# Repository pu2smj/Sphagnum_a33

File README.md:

# Sphagnum_a33
IHM with cpu Allwinner A33

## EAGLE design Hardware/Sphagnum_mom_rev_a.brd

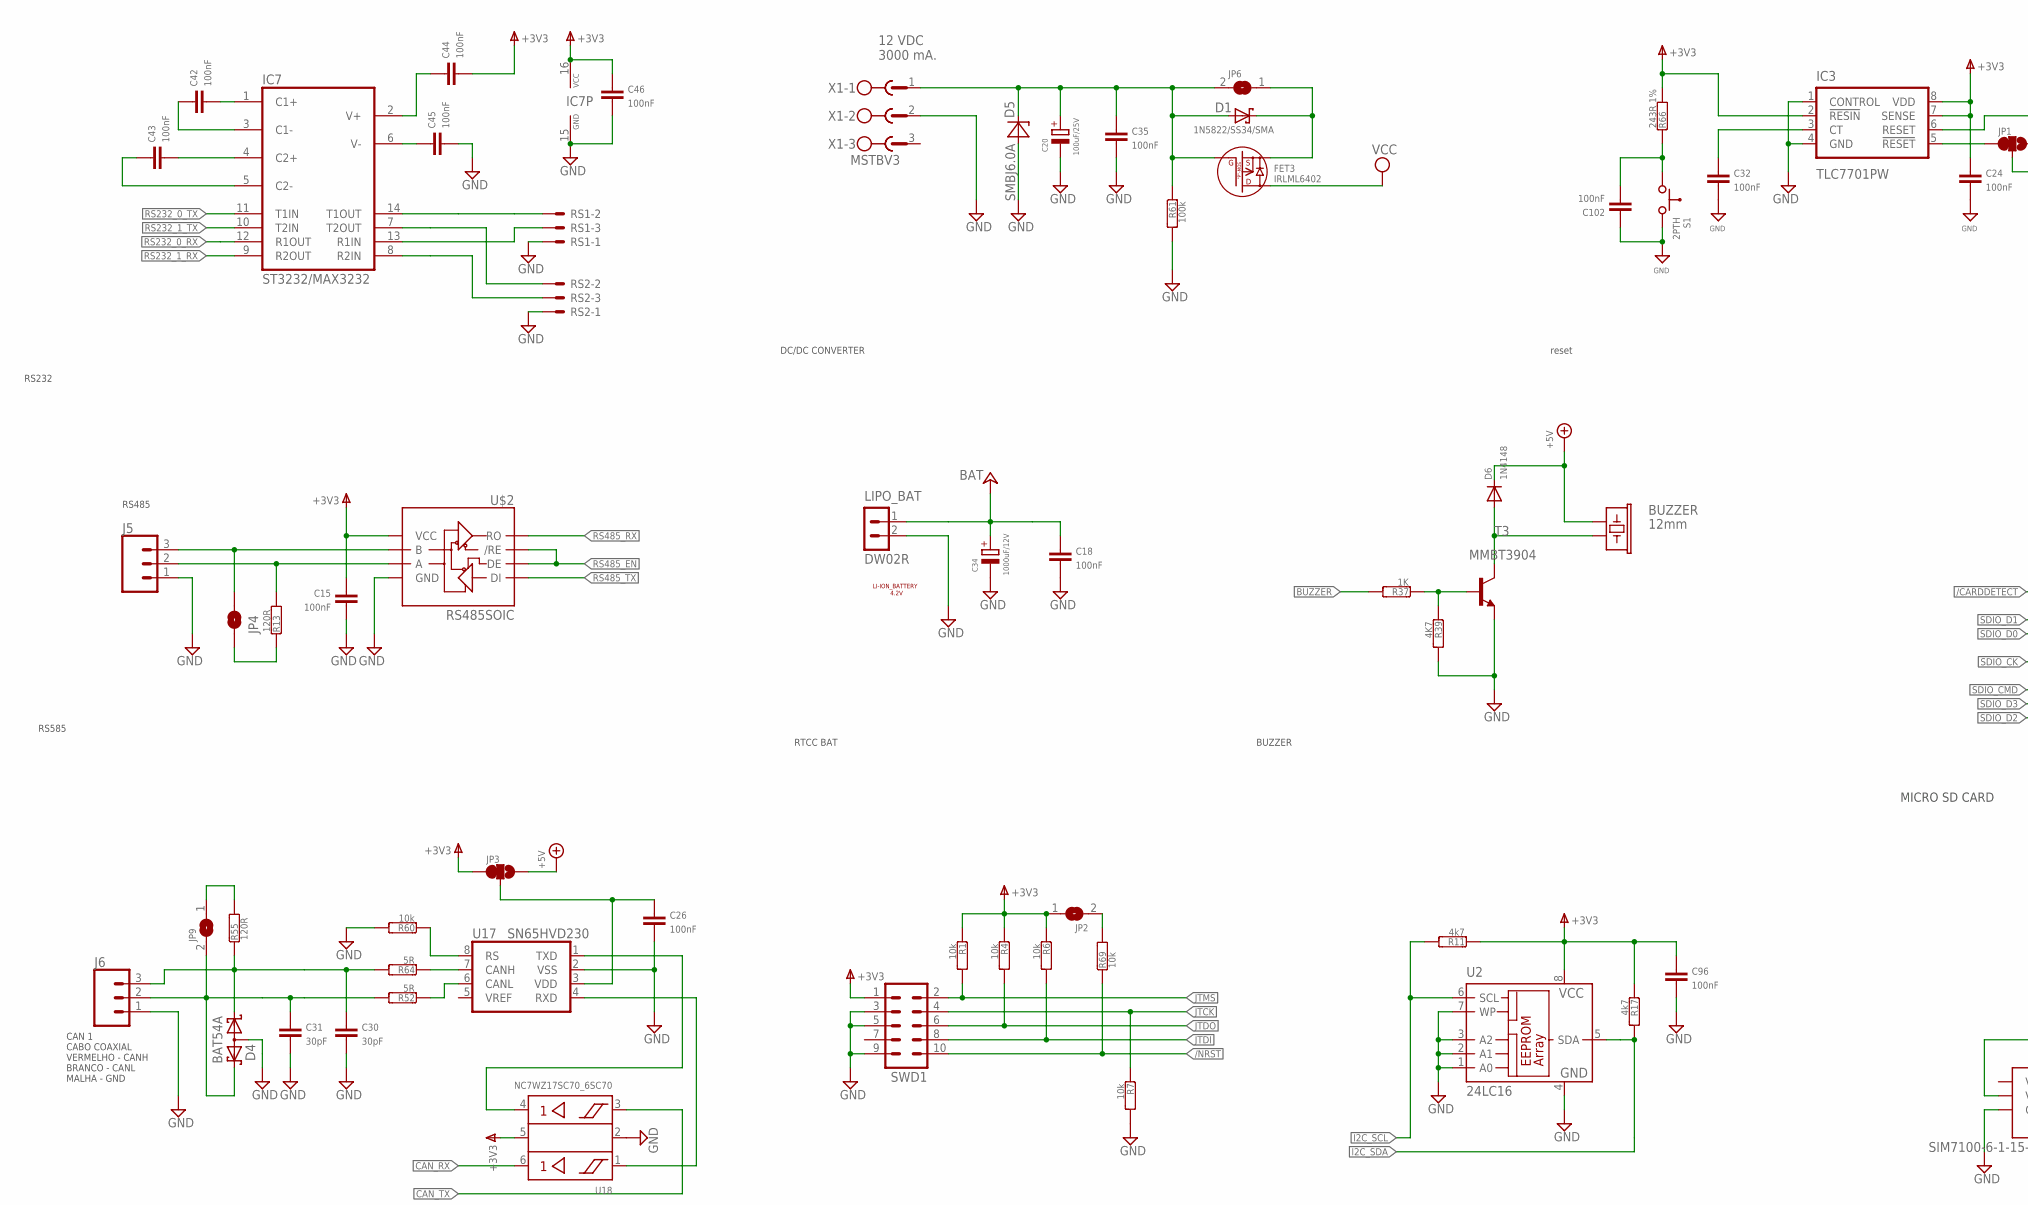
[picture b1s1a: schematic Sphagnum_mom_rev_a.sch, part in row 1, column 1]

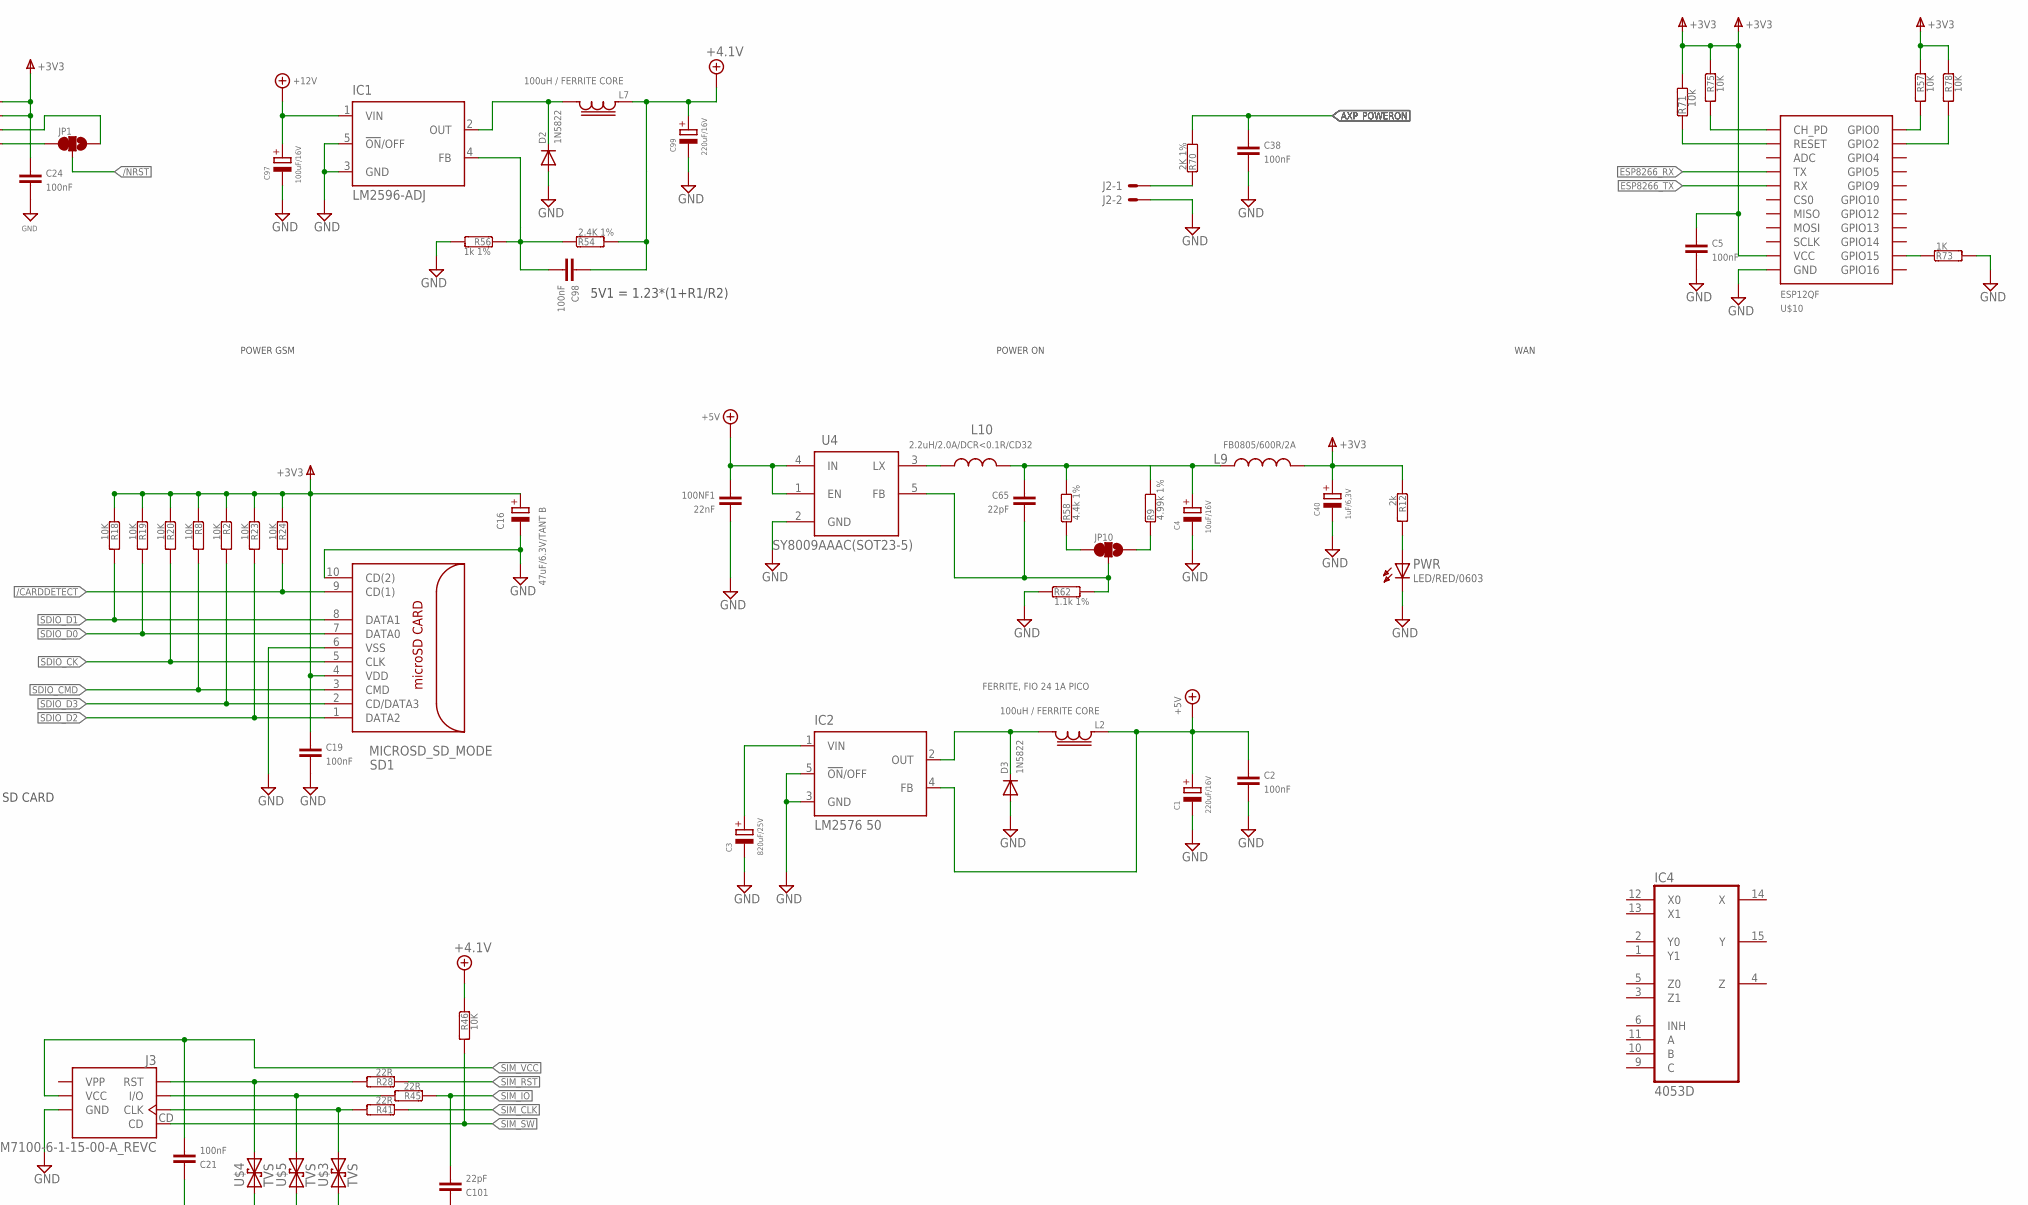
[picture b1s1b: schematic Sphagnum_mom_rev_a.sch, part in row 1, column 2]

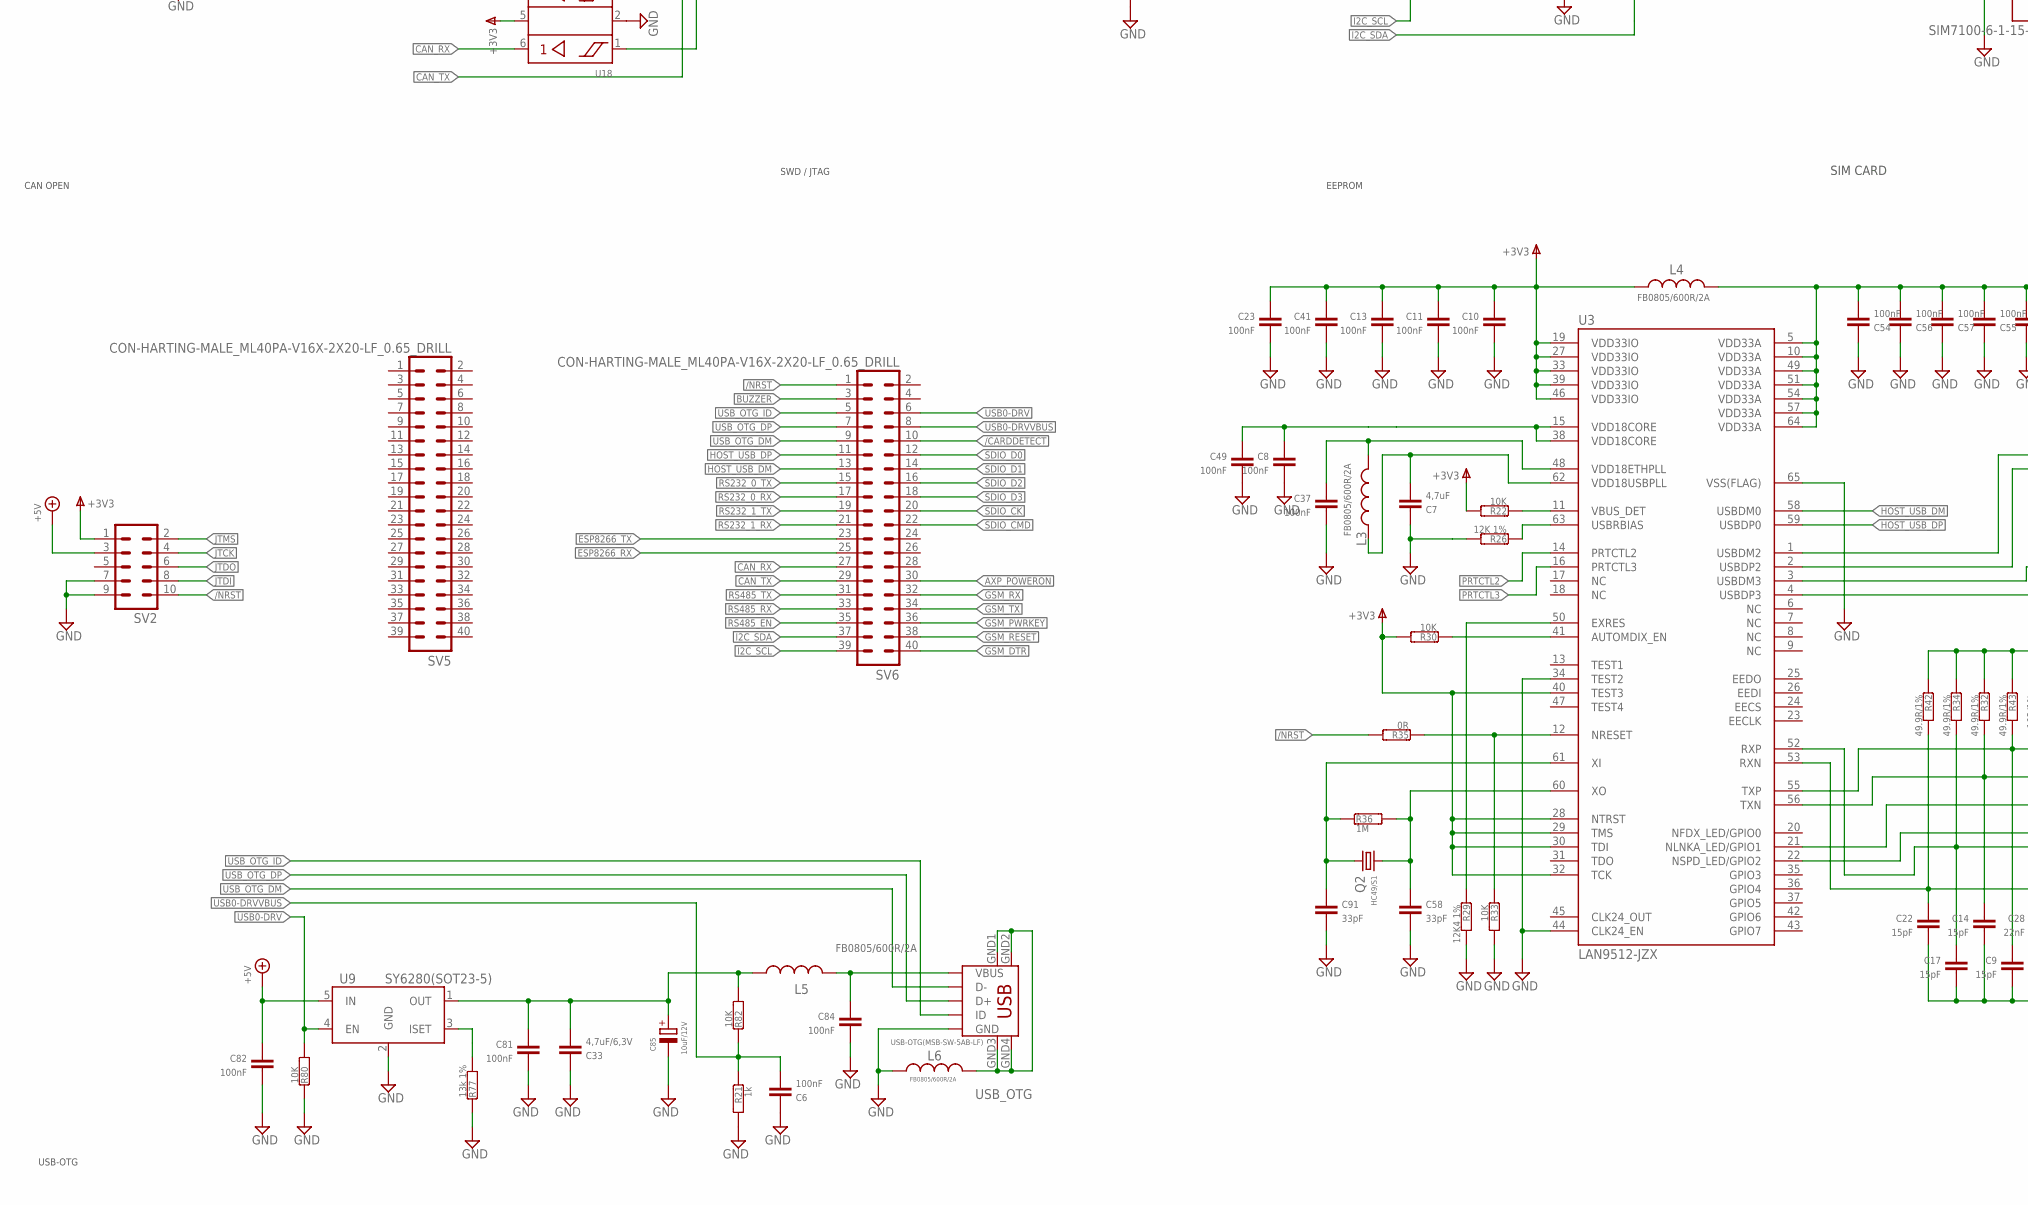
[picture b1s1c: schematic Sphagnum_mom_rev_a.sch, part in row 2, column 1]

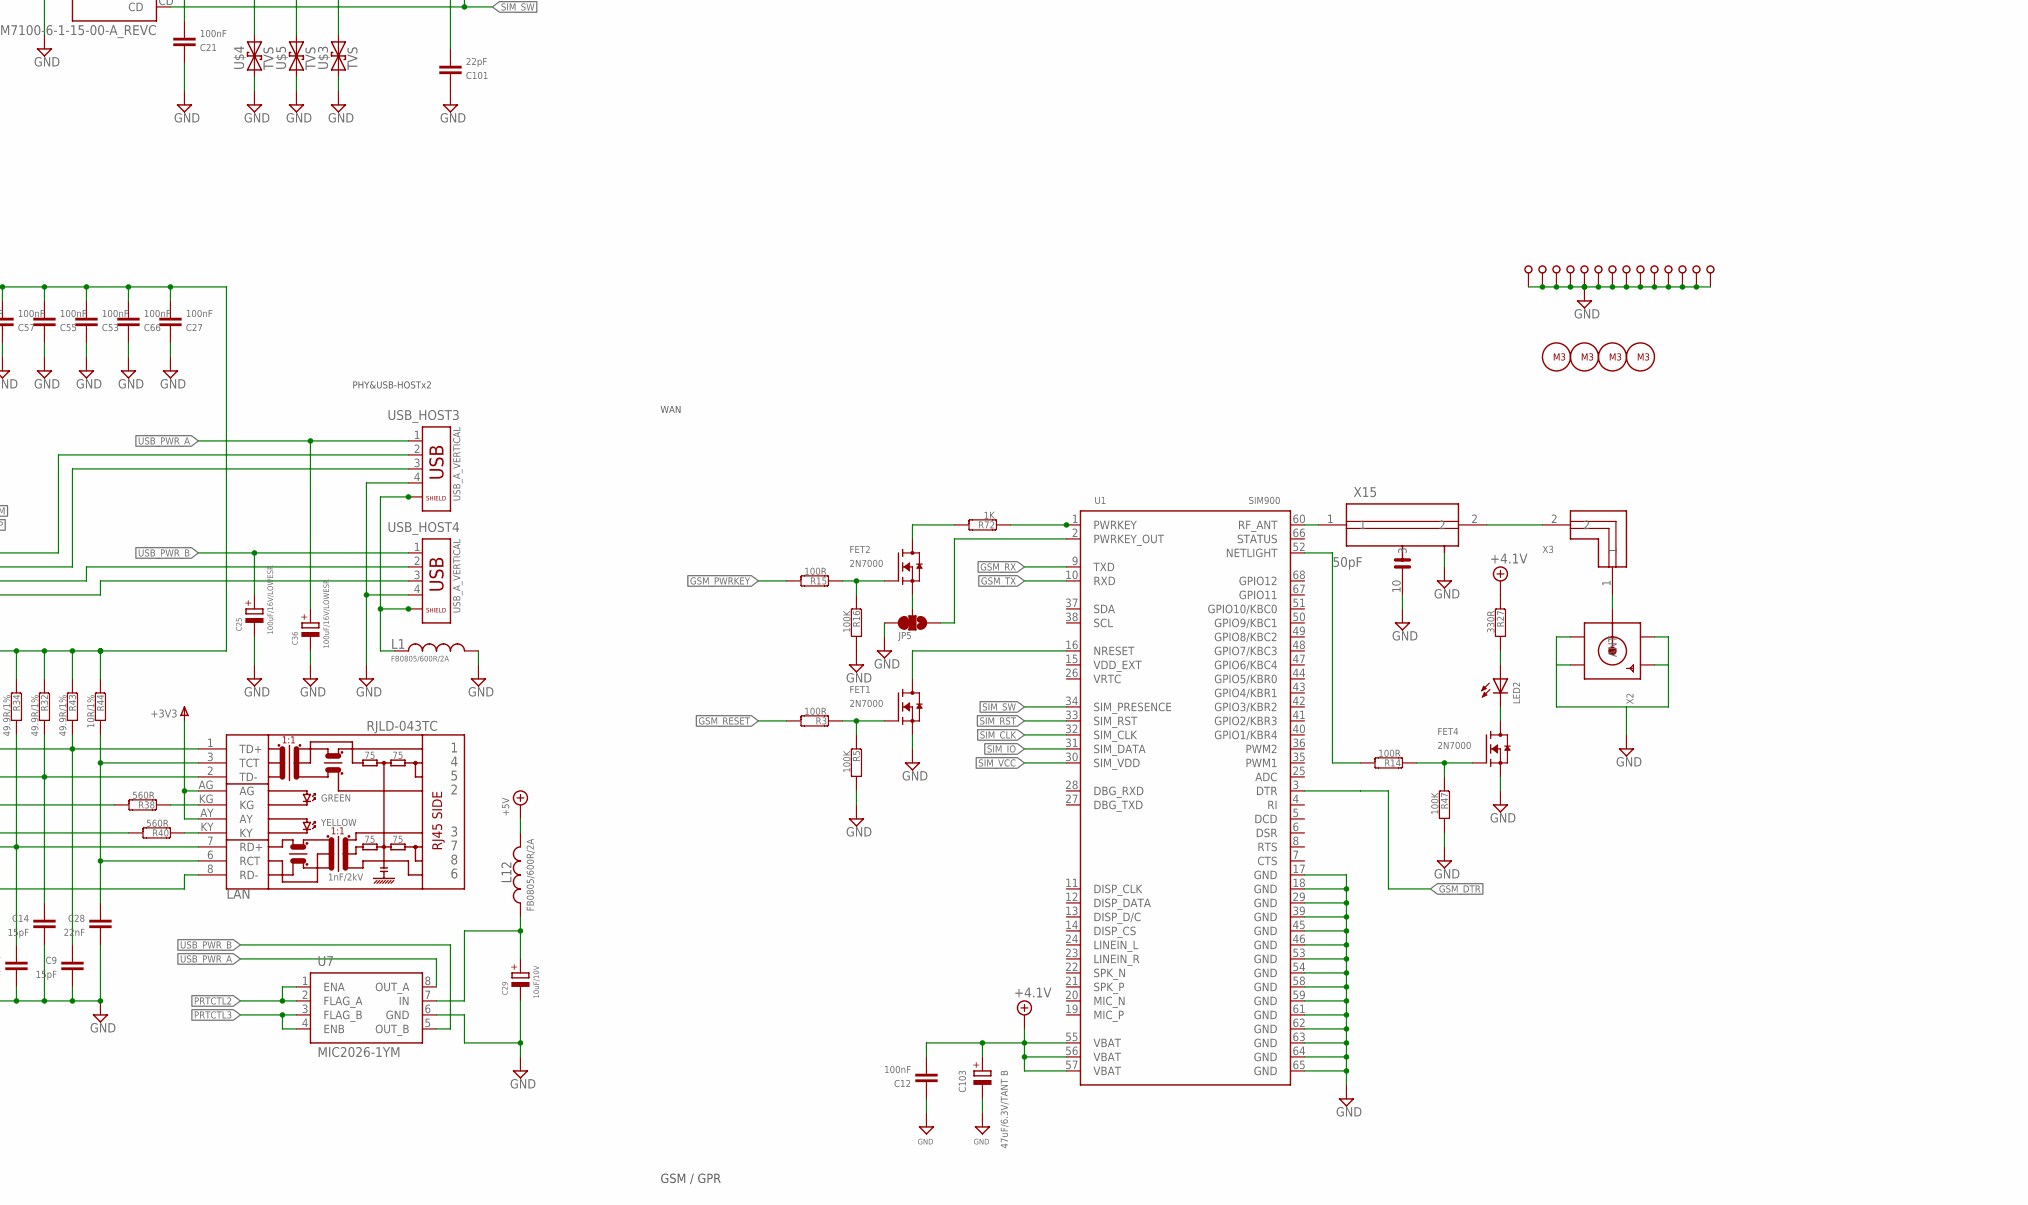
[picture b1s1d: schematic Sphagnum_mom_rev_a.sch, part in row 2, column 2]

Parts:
100NF1: 22nF; C0603
BUZZER: 12mm; BUZZER-12MM
C1, C99: 220uF/16V; E3,5-8
C2, C5, C6, C8, C10, C11, C12, C13, C15, C18, C19, C21, C23, C24, C26, C27, C32, C35, C37, C38, C41, C42, C43, C44, C45, C46, C49, C53, C54, C55, C56, C57, C66, C81, C82, C84, C96, C98, C102: 100nF; C0603
C3: 820uF/25V; E3,5-10
C4: 10uF/16V; PANASONIC_B
C7: 4,7uF; C0603
C9, C14, C17, C22: 15pF; C0603
C16, C103: 47uF/6.3V/TANT B; A/3216-18R
C20: 100uF/25V; E3,5-8
C25, C36: 100uF/16V/LOWESR; PANASONIC_D
C28: 22nF; C0603
C29: 10uF/10V; PANASONIC_B
C30, C31: 30pF; C0603
C33: 4,7uF/6,3V; C0603
C34: 1000uF/12V; PANASONIC_D
C40: 1uF/6,3V; PANASONIC_A
C58, C91: 33pF; C0603
C65, C101: 22pF; C0603
C85: 10uF/12V; PANASONIC_A
C97: 100uF/16V; E3,5-8
D1: 1N5822/SS34/SMA; MLL-41
D2, D3: 1N5822; SMA-DIODE
D4: BAT54A; SOT23
D5: SMBJ6.0A; DO214AA
D6: 1N4148; SMA-DIODE
FET1, FET2, FET4: 2N7000; SOT23
FET3: IRLML6402; SOT23
HL1, HL2, HL3, HL4: M3
IC1: LM2596-ADJ; TO263-5
IC2: LM2576 50; TO263-5
IC3: TLC7701PW; PW_R-PDSO-G08
IC4: 4053D; SO16
IC7: ST3232/MAX3232; SO16
J2: 22-27-2021-02; 6410-02
J3: SIM7100-6-1-15-00-A_REVC; GCT_SIM7100-6-1-15-00-A_REVC
J5, J6: CONN_03JST-PTH-VERT; JST-3-PTH-VERT
JP1, JP3, JP5, JP10: JUMPER_3; JUMPER_3_SMD
JP2, JP6, JP9: JUMPER_2_NO
JP4: JUMPER-SMT_2_NO_SILK; SMT-JUMPER_2_NO_SILK
L1, L5, L6: FB0805/600R/2A; 0204/5
L2, L7: 100uH / FERRITE CORE; INDUTOR
L3, L4, L9, L12: FB0805/600R/2A; L1812
L10: 2.2uH/2.0A/DCR<0.1R/CD32; CD32
LAN: RJLD-043TC; RJLD-043TC_PACK
LED2: LED0603; LED-0603
LIPO_BAT: DW02R
P1, P2, P3, P5, P7, P9, P10, P11, P12, P14, P15, P16, P17, P18: PADP; PAD
PWR: LED/RED/0603; LED-0805
Q2: HC49/S1; HC49/SMD2_THIN
R1, R4, R6, R7, R60, R69, R71: 10k; R0603
R2, R8, R18, R19, R20, R22, R23, R24, R30, R33, R46, R57, R75, R78, R80, R82: 10K; R0603
R3, R14, R15: 100R; R0603
R5, R16, R47: 100K; R0603
R9: 4.99k 1%; R0603
R11, R17: 4k7; R0603
R12: 2k; R0603
R13, R55: 120R; R0603
R21: 1k; R0603
R26: 12K 1%; R0603
R27: 330R; R0603
R28, R41, R45: 22R; R0603
R29: 12K4 1%; R0603
R32, R34, R42, R43: 49.9R/1%; R0603
R35: 0R; R0603
R36: 1M; R0603
R37, R72, R73: 1K; R0603
R38, R40: 560R; R0603
R39: 4K7; R0603
R44: 10R/1%; R0603
R52, R64: 5R; R0603
R54: 2.4K 1%; R0603
R56: 1k 1%; R0603
R58: 4.4k 1%; R0603
R61: 100k; R0603
R62: 1.1k 1%; R0603
R66: 243R 1%; R0603
R70: 2K 1%; R0603
R77: 13k 1%; R0603
RS1, RS2: 22-27-2031-03; 6410-03
S1: 2PTH; TACTILE-PTH
SD1: MICROSD_SD_MODE; MICRO_SD_CONNECTOR
SV2: ML10
SV5, SV6: CON-HARTING-MALE_ML40PA-V16X-2X20-LF_0.65_DRILL; CON-HARTING-ML_PA-V16X-2X20-LF_0.65_DRILL
SWD1: MA05-2
T3: MMBT3904; SOT23-BEC
U1: SIM900; LGA68-1.0-24.0X24.0X3.0MM
U2: 24LC16; SO-08
U3: LAN9512-JZX; QFN64
U4: SY8009AAAC(SOT23-5); SOT23-5@2
U7: MIC2026-1YM; SO-8
U9: SY6280(SOT23-5); SOT23-5
U17: SN65HVD230; SO-08_THIN
U18: NC7WZ17SC70_6SC70; SC70-6
U$2: RS485SOIC; SO08
U$3, U$4, U$5: TVS; SMA-DIODE
U$10: ESP12QF; ESP8266F
USB_HOST3, USB_HOST4: USB_A_VERTICAL; USB_A_VERTICAL_PTH
USB_OTG: USB-OTG(MSB-SW-5AB-LF); USB_MINI_9PIN-SD
X1: MSTBV3
X2: SMACONNECTOR; SMA90_DIP
X3: CHIPDESIGN_GCPW_50_OHM_L; GCPW_50_OHM_LEFT
X15: 50pF; GCPW_50_OHM_0402_SHUNT

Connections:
+3V3: C5.1, C10.1, C11.1, C13.1, C15.1, C16.+, C19.1, C23.1, C24.1, C40.+, C41.1, C44.2, C46.1, C96.1, IC3.2 (!RESIN), IC3.7 (SENSE), IC3.8 (VDD), IC7.16 (VCC), JP2.1 (4), JP3.1, L4.1, L9.2, LAN.AG, LAN.AY, R1.1, R2.1, R4.1, R6.1, R8.1, R11.1, R12.1, R17.1, R18.1, R19.1, R20.1, R22.2, R23.1, R24.1, R30.2, R57.1, R66.2, R71.2, R75.1, R78.1, SD1.4 (VDD), SV2.1, SWD1.1, U2.8 (VCC), U3.19 (VDD33IO), U3.27 (VDD33IO), U3.28 (NTRST), U3.29 (TMS), U3.30 (TDI), U3.32 (TCK), U3.33 (VDD33IO), U3.39 (VDD33IO), U3.40 (TEST3), U3.46 (VDD33IO), U18.5 (VCC), U$2.8 (VCC), U$10.VCC
+4.1V: C12.2, C98.1, C99.+, C103.+, L7.P$1, R27.1, R46.1, R54.2, U1.55 (VBAT), U1.56 (VBAT), U1.57 (VBAT)
+5V: 100NF1.1, BUZZER.+ (1), C1.+, C2.1, C82.1, D6.C, IC2.4 (FB), JP3.3, L2.P$1, L12.2, SV2.3, U4.1 (EN), U4.4 (IN), U9.5 (IN)
+12V: C97.+, IC1.1 (VIN)
+24V: C18.1, C34.+, LIPO_BAT.1
/CARDDETECT: R24.2, SD1.9 (CD(1)), SV6.10
/NRST: JP1.2, R35.2, R69.1, SV2.10, SV6.1, SWD1.10
AXP_POWERON: C38.1, R70.2, SV6.30
BUZZER: R37.2, SV6.3
CANH: C31.1, D4.2 (K2), J6.2, JP9.2 (5), R52.2
CANH2: J5.3, JP4.2, U$2.7 (B)
CAN_RX: SV6.27, U18.6
CAN_TX: SV6.29, U18.3
ESP8266_RX: SV6.25, U$10.TX
ESP8266_TX: SV6.23, U$10.RX
GND: 100NF1.2, C1.-, C2.2, C3.-, C4.-, C5.2, C6.1, C7.1, C8.2, C9.2, C10.2, C11.2, C12.1, C13.2, C14.2, C15.2, C16.-, C17.2, C18.2, C19.2, C20.-, C21.1, C22.2, C23.2, C24.2, C25.-, C26.2, C27.1, C28.2, C29.-, C30.2, C31.2, C32.2, C33.1, C34.-, C35.2, C36.-, C37.2, C38.2, C40.-, C41.2, C45.2, C46.2, C49.2, C53.1, C54.1, C55.1, C56.1, C57.1, C58.2, C66.1, C81.2, C82.2, C84.2, C85.-, C91.2, C96.2, C97.-, C99.-, C101.1, C102.1, C103.-, D2.A, D3.A, D4.3 (AA), D5.A, FET1.2 (S), FET4.2 (S), IC1.3 (GND), IC1.5 (!ON!/OFF), IC2.3 (GND), IC2.5 (!ON!/OFF), IC3.1 (CONTROL), IC3.4 (GND), IC4.8 (GND), IC7.15 (GND), J2.2, J3.C5 (GND), J5.1, J6.1, JP5.1, L1.2, L6.1, LIPO_BAT.2, P1.A, P2.A, P3.A, P5.A, P7.A, P9.A, P10.A, P11.A, P12.A, P14.A, P15.A, P16.A, P17.A, P18.A, PWR.C, R5.2, R7.2, R16.2, R21.2, R26.2, R29.2, R33.2, R39.2, R47.2, R56.2, R60.2, R61.2, R62.1, R73.2, R77.1, R80.1, RS1.1, RS2.1, S1.3 (2), SD1.6 (VSS), SD1.10 (CD(2)), SV2.7, SV2.9, SWD1.3, SWD1.5, SWD1.9, T3.E, U1.17 (GND), U1.18 (GND), U1.29 (GND), U1.39 (GND), U1.45 (GND), U1.46 (GND), U1.53 (GND), U1.54 (GND), U1.58 (GND), U1.59 (GND), U1.61 (GND), U1.62 (GND), U1.63 (GND), U1.64 (GND), U1.65 (GND), U2.1 (A0), U2.2 (A1), U2.3 (A2), U2.4 (GND), U2.7 (WP), U3.34 (TEST2), U3.44 (CLK24_EN), U3.65 (VSS(FLAG)), U4.2 (GND), U7.6 (GND), U9.2 (GND), U17.2 (VSS), U18.2 (GND), U$2.5 (GND), U$3.A (1), U$4.A (1), U$5.A (1), U$10.GND, USB_HOST3.4, USB_HOST4.4, USB_OTG.GND, X1.2, X2.GND1, X2.GND2, X2.GND3, X2.GND4, X15.3 (GND), X15.4 (GND), X15.5 (GND), X15.6 (GND), X15.7 (GND), X15.8 (GND), X15.9 (GND), X15.10 (3), X15.11 (GND), X15.12 (GND)
GSM_DTR: SV6.40, U1.3 (DTR)
GSM_PWRKEY: R15.2, SV6.36
GSM_RESET: R3.2, SV6.38
GSM_RX: SV6.32, U1.9 (TXD)
GSM_TX: SV6.34, U1.10 (RXD)
HOST_USB_DM: SV6.13, U3.58 (USBDM0)
HOST_USB_DP: SV6.11, U3.59 (USBDP0)
I2C_SCL: R11.2, SV6.39, U2.6 (SCL)
I2C_SDA: R17.2, SV6.37, U2.5 (SDA)
JTCK: R7.1, SV2.4, SWD1.4
JTDI: R6.2, SV2.8, SWD1.8
JTDO: R4.2, SV2.6, SWD1.6
JTMS: R1.2, SV2.2, SWD1.2
unnamed: PWR.A, R12.2
unnamed: R60.1, U17.8 (RS)
unnamed: C37.1, L3.2, U3.48 (VDD18ETHPLL)
unnamed: R77.2, U9.3 (ISET)
unnamed: C29.+, L12.1, U7.7 (IN)
unnamed: IC3.5 (!RESET), JP1.1
unnamed: J2.1, R70.1
unnamed: C7.2, L3.1, U3.62 (VDD18USBPLL)
unnamed: L1.1, USB_HOST3.P$3 (5), USB_HOST3.P$4 (6), USB_HOST4.P$3 (5), USB_HOST4.P$4 (6)
unnamed: U3.2 (USBDP2), USB_HOST3.3
unnamed: U3.3 (USBDM3), USB_HOST4.2
unnamed: U3.4 (USBDP3), USB_HOST4.3
unnamed: FET1.1 (G), R3.1, R5.1
unnamed: BUZZER.- (2), D6.A, T3.C
unnamed: R14.2, U1.52 (NETLIGHT)
unnamed: R37.1, R39.1, T3.B
unnamed: JP2.2 (5), R69.2
unnamed: D2.C, IC1.2 (OUT), L7.P$2
unnamed: FET4.3 (D), LED2.C
unnamed: JP4.1, R13.1
unnamed: C30.1, D4.1 (K1), J6.3, R55.1, R64.2
unnamed: JP9.1 (4), R55.2
unnamed: FET1.3 (D), U1.16 (NRESET)
unnamed: IC7.7 (T2OUT), RS2.2
unnamed: IC7.8 (R2IN), RS2.3
unnamed: LED2.A, R27.2
unnamed: FET2.3 (D), R72.2
unnamed: FET2.1 (G), R15.1, R16.1
unnamed: U1.60 (RF_ANT), X15.1
unnamed: J3.C2 (RST), R28.2, U$4.C (2)
unnamed: X3.2, X15.2
unnamed: C20.+, C35.1, D1.A, D5.C, FET3.1 (G), JP6.2 (5), R61.1, X1.1
unnamed: D1.K (C), FET3.2 (S), JP6.1 (4)
unnamed: R71.1, U$10.RST (RESET)
unnamed: FET4.1 (G), R14.1, R47.1
unnamed: J3.C7 (I/O), R45.2, U$5.C (2)
unnamed: FET2.2 (S), JP5.2
unnamed: C8.1, C49.1, U3.15 (VDD18CORE), U3.38 (VDD18CORE)
unnamed: J3.C3 (CLK), R41.2, U$3.C (2)
unnamed: R75.2, U$10.EN (CH_PD)
unnamed: R26.1, U3.63 (USBRBIAS)
unnamed: R29.1, U3.50 (EXRES)
unnamed: R30.1, U3.41 (AUTOMDIX_EN)
unnamed: C91.1, Q2.2, R36.1, U3.61 (XI)
unnamed: C58.1, Q2.1, R36.2, U3.60 (XO)
unnamed: R78.2, U$10.GPIO2
unnamed: R38.2, U3.21 (NLNKA_LED/GPIO1)
unnamed: R40.2, U3.22 (NSPD_LED/GPIO2)
unnamed: LAN.KG, R38.1
unnamed: LAN.KY, R40.1
unnamed: C22.1, LAN.8 (RD-), R42.2, U3.53 (RXN)
unnamed: R73.1, U$10.GPIO15
unnamed: C17.1, LAN.7 (RD+), R34.2, U3.52 (RXP)
unnamed: C14.1, LAN.2 (TD-), R32.2, U3.56 (TXN)
unnamed: C9.1, LAN.1 (TD+), R43.2, U3.55 (TXP)
unnamed: R57.2, U$10.GPIO0
unnamed: C28.1, LAN.3 (TCT), LAN.6 (RCT), R44.2
unnamed: U3.1 (USBDM2), USB_HOST3.2
unnamed: R72.1, U1.1 (PWRKEY)
unnamed: JP5.3, U1.2 (PWRKEY_OUT)
unnamed: C3.+, IC2.1 (VIN)
unnamed: X2.ANTENNA (ANT), X3.1
unnamed: R33.1, R35.1, U3.12 (NRESET)
unnamed: C65.2, JP10.2, R62.2, U4.5 (FB)
unnamed: JP10.1, R58.1
unnamed: JP10.3, R9.1
unnamed: C4.+, C65.1, L9.1, L10.2, R9.2, R58.2
unnamed: C32.1, IC3.3 (CT)
unnamed: D3.C, IC2.2 (OUT), L2.P$2
unnamed: IC3.6 (RESET), JP1.3
unnamed: L10.1, U4.3 (LX)
unnamed: C27.2, C53.2, C54.2, C55.2, C56.2, C57.2, C66.2, L4.2, R32.1, R34.1, R42.1, R43.1, R44.1, U3.5 (VDD33A), U3.10 (VDD33A), U3.49 (VDD33A), U3.51 (VDD33A), U3.54 (VDD33A), U3.57 (VDD33A), U3.64 (VDD33A)
unnamed: R22.1, U3.11 (VBUS_DET)
unnamed: C33.2, C81.1, C85.+, L5.2, R82.2, U9.1 (OUT)
unnamed: J5.2, R13.2, U$2.6 (A)
unnamed: C26.1, JP3.2, U17.3 (VDD)
unnamed: R64.1, U17.7 (CANH)
unnamed: U17.1 (TXD), U18.4
unnamed: R52.1, U17.6 (CANL)
unnamed: U17.4 (RXD), U18.1
unnamed: C42.2, IC7.1 (C1+)
unnamed: C43.2, IC7.4 (C2+)
unnamed: C42.1, IC7.3 (C1-)
unnamed: C43.1, IC7.5 (C2-)
unnamed: C44.1, IC7.2 (V+)
unnamed: C45.1, IC7.6 (V-)
unnamed: L6.2, USB_OTG.GND1, USB_OTG.GND2, USB_OTG.GND3, USB_OTG.GND4
unnamed: C84.1, L5.1, USB_OTG.VBUS
NRST1: C102.2, R66.1, S1.1
PRTCTL2: U3.14 (PRTCTL2), U7.1 (ENA), U7.2 (FLAG_A)
PRTCTL3: U3.16 (PRTCTL3), U7.3 (FLAG_B), U7.4 (ENB)
R1IN: IC7.13 (R1IN), RS1.3
RS232_0_RX: IC7.12 (R1OUT), SV6.17
RS232_0_TX: IC7.11 (T1IN), SV6.15
RS232_1_RX: IC7.9 (R2OUT), SV6.21
RS232_1_TX: IC7.10 (T2IN), SV6.19
RS485_EN: SV6.35, U$2.2 (/RE), U$2.3 (DE)
RS485_RX: SV6.33, U$2.1 (RO)
RS485_TX: SV6.31, U$2.4 (DI)
SDIO_CK: R20.2, SD1.5 (CLK), SV6.20
SDIO_CMD: R8.2, SD1.3 (CMD), SV6.22
SDIO_D0: R19.2, SD1.7 (DATA0), SV6.12
SDIO_D1: R18.2, SD1.8 (DATA1), SV6.14
SDIO_D2: R23.2, SD1.1 (DATA2), SV6.16
SDIO_D3: R2.2, SD1.2 (CD/DATA3), SV6.18
SIM_CLK: R41.1, U1.32 (SIM_CLK)
SIM_IO: C101.2, R45.1, U1.31 (SIM_DATA)
SIM_RST: R28.1, U1.33 (SIM_RST)
SIM_SW: J3.CD, R46.2, U1.34 (SIM_PRESENCE)
SIM_VCC: C21.2, J3.C1 (VCC), U1.30 (SIM_VDD)
T1OUT: IC7.14 (T1OUT), RS1.2
USB0-DRV: R80.2, SV6.6, U9.4 (EN)
USB0-DRVVBUS: C6.2, R21.1, R82.1, SV6.8
USB_OTG_DM: SV6.9, USB_OTG.D-
USB_OTG_DP: SV6.7, USB_OTG.D+
USB_OTG_ID: SV6.5, USB_OTG.ID
USB_OTG_VBUS2: C98.2, IC1.4 (FB), R54.1, R56.1
USB_PWR_A: C36.+, U7.8 (OUT_A), USB_HOST3.1
USB_PWR_B: C25.+, U7.5 (OUT_B), USB_HOST4.1
VCC: FET3.3 (D), IC4.16 (VCC)
VEE: IC4.7 (VEE)
VPP: J3.C6 (VPP)

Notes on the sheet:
DC/DC CONVERTER
FERRITE, FIO 24 1A PICO
12 VDC 3000 mA.
MICRO SD CARD
RTCC BAT
BUZZER
CAN OPEN
CAN 1 CABO COAXIAL VERMELHO - CANH BRANCO - CANL MALHA - GND
RS485
RS585
RS232
USB-OTG
PHY&USB-HOSTx2
SWD / JTAG
EEPROM
SIM CARD
LI-ION_BATTERY
4.2V
POWER ON
5V1 = 1.23*(1+R1/R2)
GSM / GPR
POWER GSM
WAN
reset

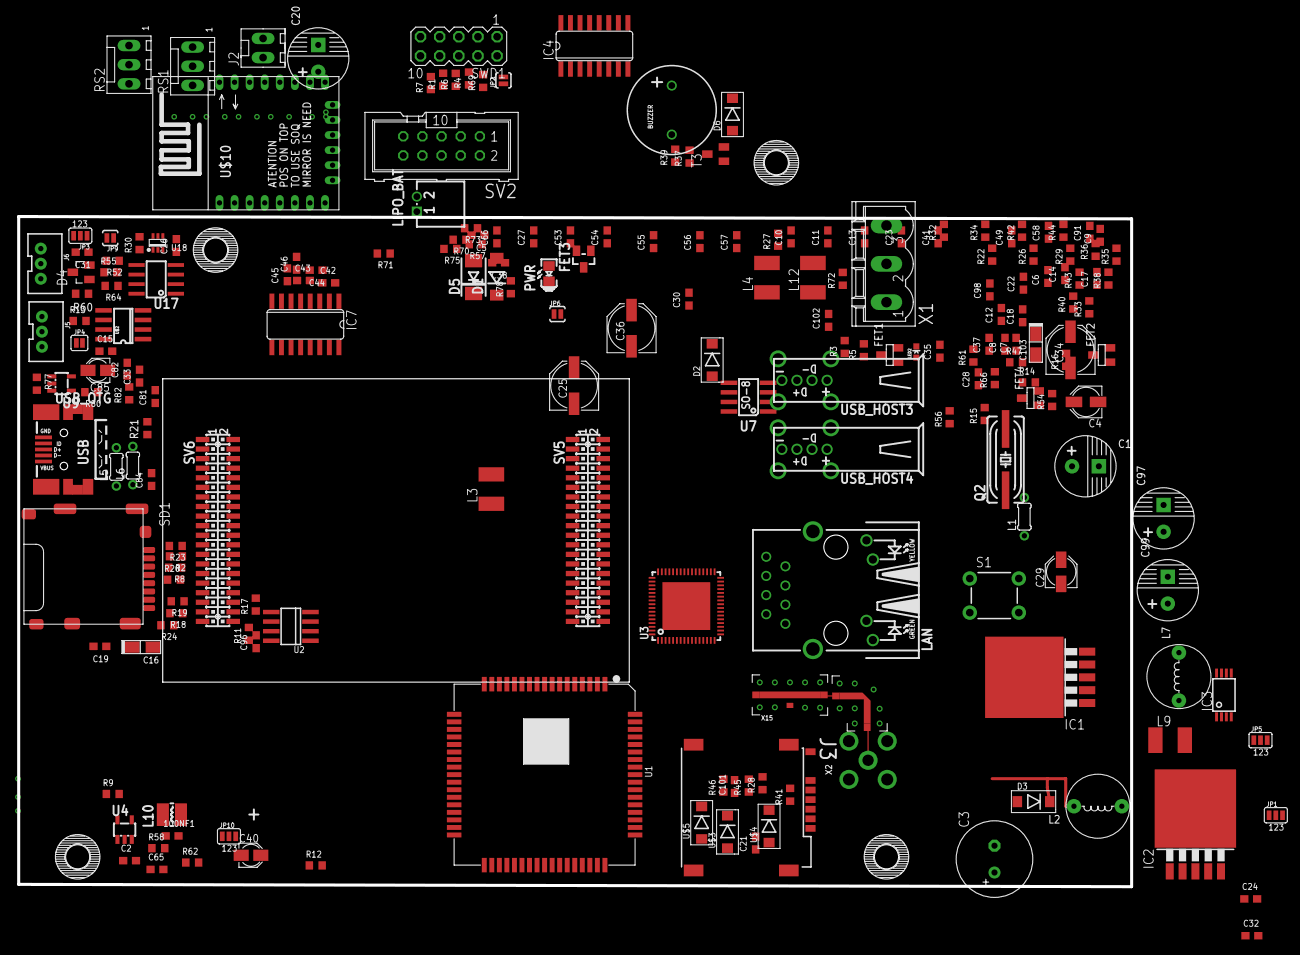
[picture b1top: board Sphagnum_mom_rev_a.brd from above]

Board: 2 copper layers, 147.6 x 88.9 mm, 222 parts (0 on the bottom side), 149 nets.

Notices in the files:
parts and their libraries:
SparkFun-Jumpers: Licensing: Creative Commons ShareAlike 4.0 International - https://creativecommons.org/licenses/by-sa/4.0
